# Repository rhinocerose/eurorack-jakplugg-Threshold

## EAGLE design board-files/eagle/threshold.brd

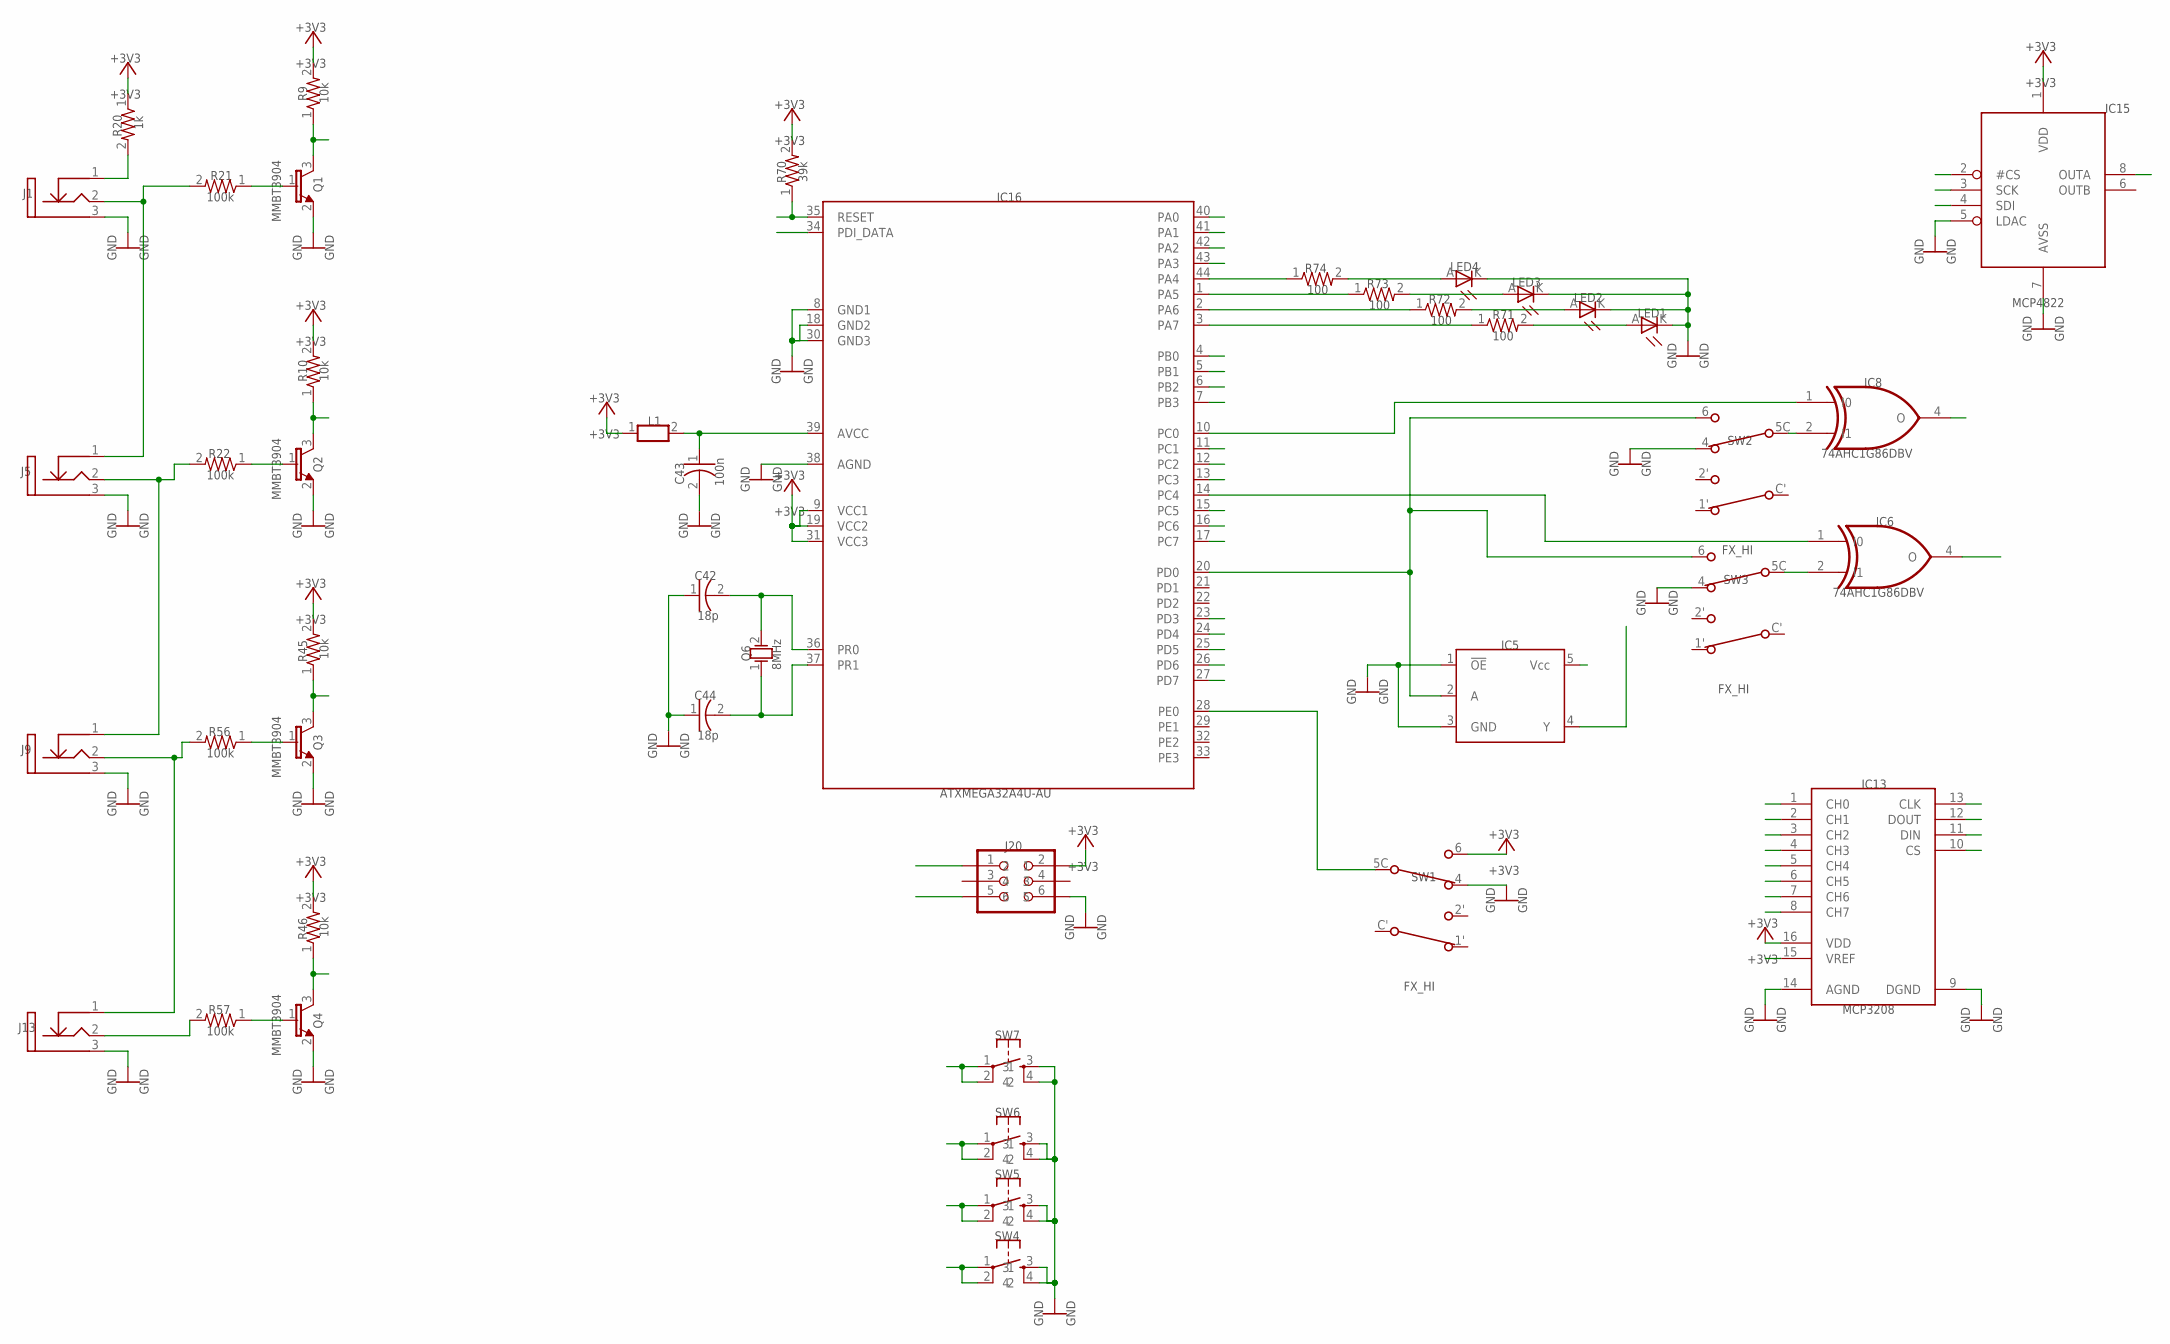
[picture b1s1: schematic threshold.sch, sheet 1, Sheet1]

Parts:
C42, C44: 18p; CAP_0603
C43: 100n; CAP_0603
IC5: 74AHC1G125GV; SOT23-5
IC6, IC8: 74AHC1G86DBV; SOT23-5
IC13: MCP3208; SO16
IC15: MCP4822; SO08
IC16: ATXMEGA32A4U-AU; TQFP44
J1, J5, J9, J13: THONKICONN; THONKICONN_JACK
J20: AVR_SPI_PRG_6PTH; 2X3
L1: WE-CBF_0603; 0603
LED1, LED2, LED3, LED4: LED3MM
Q1, Q2, Q3, Q4: MMBT3904; SOT23
Q6: 8MHz; TSC_7A_CRYSTAL
R9, R10, R45, R46: 10k; RES_0603
R20: 1k; RES_0603
R21, R22, R56, R57: 100k; RES_0603
R70: 39k; RES_0603
R71, R72, R73, R74: 100; RES_0603
SW1, SW2, SW3: FX_HI; PVB6I
SW4, SW5, SW6, SW7: TAC_SWITCHPTH; TACTILE-PTH

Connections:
+3V3: IC5.5 (Vcc), IC13.16 (VDD), IC15.1 (VDD), IC16.9 (VCC1), IC16.19 (VCC2), IC16.31 (VCC3), J20.2, L1.1, R9.2, R10.2, R20.1, R45.2, R46.2, R70.2, SW1.6 (C2); also elsewhere on the board
ADC_MISO: IC13.12 (DOUT), IC16.26 (PD6)
ADC_MOSI: IC13.11 (DIN), IC16.25 (PD5)
ADC_SCK: IC13.13 (CLK), IC16.27 (PD7)
ADC_SS: IC13.10 (CS), IC16.23 (PD3)
AREF: IC13.15 (VREF); also elsewhere on the board
CH1: IC13.1 (CH0); also elsewhere on the board
CH2: IC13.2 (CH1); also elsewhere on the board
CH3: IC13.5 (CH4); also elsewhere on the board
CH4: IC13.6 (CH5); also elsewhere on the board
CH5: IC13.3 (CH2); also elsewhere on the board
CH6: IC13.4 (CH3); also elsewhere on the board
CH7: IC13.7 (CH6); also elsewhere on the board
CH8: IC13.8 (CH7); also elsewhere on the board
CHANNEL1: IC5.4 (Y); also elsewhere on the board
CHANNEL2: IC6.4 (O); also elsewhere on the board
CHANNEL3: IC8.4 (O); also elsewhere on the board
CHANNEL4: IC15.8 (OUTA); also elsewhere on the board
DAC_MOSI: IC15.4 (SDI), IC16.17 (PC7)
DAC_SCK: IC15.3 (SCK), IC16.15 (PC5)
DAC_SS: IC15.2 (#CS), IC16.16 (PC6)
GATE1: IC16.40 (PA0), Q1.3 (C), R9.1
GATE1_IN: J1.2 (Tip), J5.1 (TN), R21.2
GATE1_LED: LED4.A, R74.2
GATE2: IC16.41 (PA1), Q2.3 (C), R10.1
GATE2_IN: J5.2 (Tip), J9.1 (TN), R22.2
GATE2_LED: LED3.A, R73.2
GATE3: IC16.42 (PA2), Q3.3 (C), R45.1
GATE3_IN: J9.2 (Tip), J13.1 (TN), R56.2
GATE3_LED: LED2.A, R72.2
GATE4: IC16.43 (PA3), Q4.3 (C), R46.1
GATE4_IN: J13.2 (Tip), R57.2
GATE4_LED: LED1.A, R71.2
GND: C42.1, C43.2, C44.1, IC5.1 (!OE!), IC5.3 (GND), IC13.9 (DGND), IC13.14 (AGND), IC15.5 (LDAC), IC15.7 (AVSS), IC16.8 (GND1), IC16.18 (GND2), IC16.30 (GND3), IC16.38 (AGND), J1.3 (GND), J5.3 (GND), J9.3 (GND), J13.3 (GND), J20.6, LED1.K (C), LED2.K (C), LED3.K (C), LED4.K (C), Q1.2 (E), Q2.2 (E), Q3.2 (E), Q4.2 (E), SW1.3, SW1.4 (C3), SW2.3, SW2.4 (C3), SW3.3, SW3.4 (C3), SW4.3, SW4.4, SW5.3, SW5.4, SW6.3, SW6.4, SW7.3, SW7.4; also elsewhere on the board
MIDI_IN: IC16.12 (PC2); also elsewhere on the board
unnamed: Q1.1 (B), R21.1
unnamed: Q2.1 (B), R22.1
unnamed: Q3.1 (B), R56.1
unnamed: IC16.44 (PA4), R74.1
unnamed: IC16.1 (PA5), R73.1
unnamed: IC16.2 (PA6), R72.1
unnamed: IC16.3 (PA7), R71.1
unnamed: J1.1 (TN), R20.2
unnamed: IC6.1 (I0), IC16.14 (PC4)
unnamed: IC8.2 (I1), SW2.5C (C1)
unnamed: IC6.2 (I1), SW3.5C (C1)
unnamed: C43.1, IC16.39 (AVCC), L1.2
unnamed: IC8.1 (I0), IC16.10 (PC0)
unnamed: IC5.2 (A), IC16.20 (PD0), SW2.6 (C2), SW3.6 (C2)
unnamed: C44.2, IC16.37 (PR1), Q6.1 (OSC1)
unnamed: C42.2, IC16.36 (PR0), Q6.2 (OSC2)
unnamed: Q4.1 (B), R57.1
NES_TRIANGLE_CLK: IC16.24 (PD4); also elsewhere on the board
PDICLK: IC16.35 (RESET), J20.5, R70.1
PDIDATA: IC16.34 (PDI_DATA), J20.1
SW1: IC16.4 (PB0), SW7.1, SW7.2
SW2: IC16.5 (PB1), SW6.1, SW6.2
SW3: IC16.6 (PB2), SW5.1, SW5.2
SW4: IC16.7 (PB3), SW4.1, SW4.2
SW_MIDI_LEARN: IC16.11 (PC1); also elsewhere on the board
SW_MIDI_MODE: IC16.13 (PC3); also elsewhere on the board
SYNC_SWITCH: IC16.28 (PE0), SW1.5C (C1)

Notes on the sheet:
+3V3
C42
18p
C43
100n
C44
GND
IC5
IC6
74AHC1G86DBV
IC8
IC13
MCP3208
IC15
MCP4822
IC16
ATXMEGA32A4U-AU
J13
J20
LED1
LED2
LED3
LED4
MMBT3904
8MHz
10k
R10
R20
R21
100k
R22
R45
R46
R56
R57
R70
39k
R71
100
R72

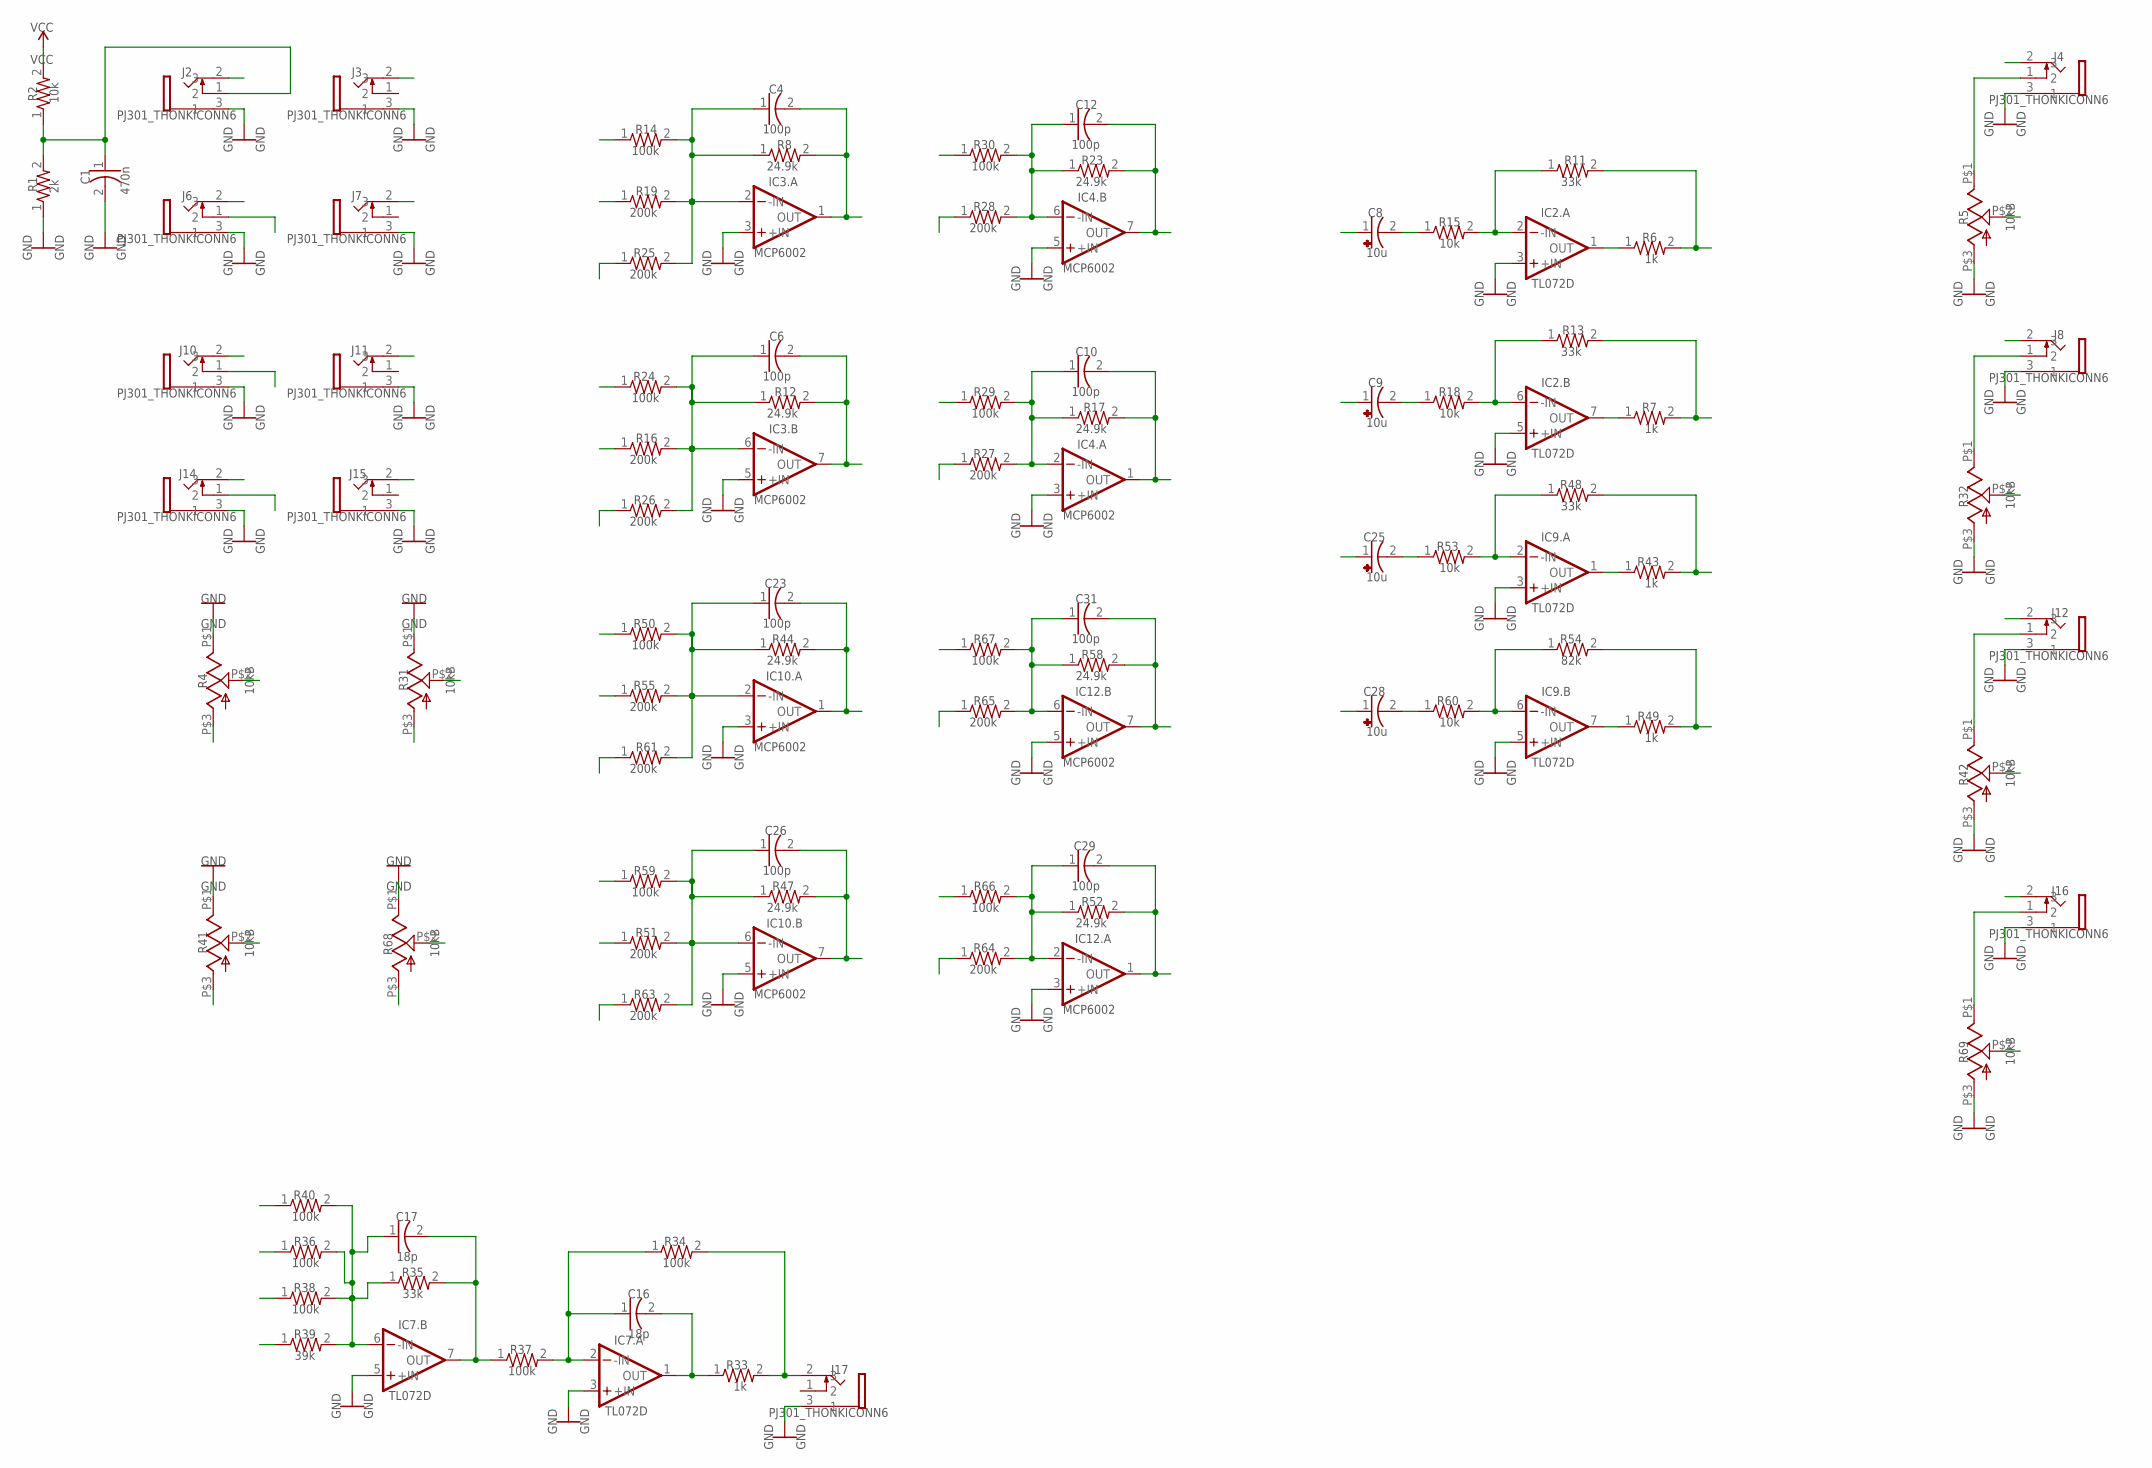
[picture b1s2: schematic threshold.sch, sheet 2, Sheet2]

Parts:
C1: 470n; CAP_0603
C4, C6, C10, C12, C23, C26, C29, C31: 100p; CAP_0603
C8, C9, C25, C28: 10u; CAP_1206
C16, C17: 18p; CAP_0603
IC2, IC7, IC9: TL072D; SO08_23
IC3, IC4, IC10, IC12: MCP6002; SO08_23
J2, J3, J4, J6, J7, J8, J10, J11, J12, J14, J15, J16, J17: PJ301_THONKICONN6; THONKICONN
R1: 2k; RES_0603
R2, R15, R18, R53, R60: 10k; RES_0603
R4, R5, R31, R32, R41, R42, R68, R69: 10kB; ALPS_POT_VERTICAL_PS
R6, R7, R33, R43, R49: 1k; RES_0603
R8, R12, R17, R23, R44, R47, R52, R58: 24.9k; RES_0603
R11, R13, R35, R48: 33k; RES_0603
R14, R24, R29, R30, R34, R36, R37, R38, R40, R50, R59, R66, R67: 100k; RES_0603
R16, R19, R25, R26, R27, R28, R51, R55, R61, R63, R64, R65: 200k; RES_0603
R39: 39k; RES_0603
R54: 82k; RES_0603

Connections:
AREF_-10: R4.P$3 (A), R25.1, R26.1, R27.1, R28.1, R31.P$3 (A), R41.P$3 (A), R61.1, R63.1, R64.1, R65.1, R68.P$3 (A); also elsewhere on the board
CH1: C4.2, IC3.1 (OUT), R8.2; also elsewhere on the board
CH2: C6.2, IC3.7 (OUT), R12.2; also elsewhere on the board
CH3: C23.2, IC10.1 (OUT), R44.2; also elsewhere on the board
CH4: C26.2, IC10.7 (OUT), R47.2; also elsewhere on the board
CH5: C12.2, IC4.7 (OUT), R23.2; also elsewhere on the board
CH6: C10.2, IC4.1 (OUT), R17.2; also elsewhere on the board
CH7: C31.2, IC12.7 (OUT), R58.2; also elsewhere on the board
CH8: C29.2, IC12.1 (OUT), R52.2; also elsewhere on the board
CHANNEL1: C8.1 (+); also elsewhere on the board
CHANNEL1_BUFFERED: J4.2 (3), R6.2, R11.2
CHANNEL1_RETURN: R5.P$2 (S), R40.1
CHANNEL2: C9.1 (+); also elsewhere on the board
CHANNEL2_BUFFERED: J8.2 (3), R7.2, R13.2
CHANNEL2_RETURN: R32.P$2 (S), R36.1
CHANNEL3: C25.1 (+); also elsewhere on the board
CHANNEL3_BUFFERED: J12.2 (3), R43.2, R48.2
CHANNEL3_RETURN: R38.1, R42.P$2 (S)
CHANNEL4: C28.1 (+); also elsewhere on the board
CHANNEL4_BUFFERED: J16.2 (3), R49.2, R54.2
CHANNEL4_RETURN: R39.1, R69.P$2 (S)
COARSE1: R4.P$2 (S), R19.1
COARSE2: R16.1, R31.P$2 (S)
COARSE3: R41.P$2 (S), R55.1
COARSE4: R51.1, R68.P$2 (S)
CV1: J2.2 (3), J6.1 (2), R14.1
CV2: J6.2 (3), J10.1 (2), R24.1
CV3: J10.2 (3), J14.1 (2), R50.1
CV4: J14.2 (3), R59.1
FM1: J3.2 (3), R30.1
FM2: J7.2 (3), R29.1
FM3: J11.2 (3), R67.1
FM4: J15.2 (3), R66.1
GND: C1.2, IC2.3 (+IN), IC2.5 (+IN), IC3.3 (+IN), IC3.5 (+IN), IC4.3 (+IN), IC4.5 (+IN), IC7.3 (+IN), IC7.5 (+IN), IC9.3 (+IN), IC9.5 (+IN), IC10.3 (+IN), IC10.5 (+IN), IC12.3 (+IN), IC12.5 (+IN), J2.3 (1), J3.3 (1), J4.3 (1), J6.3 (1), J7.3 (1), J8.3 (1), J10.3 (1), J11.3 (1), J12.3 (1), J14.3 (1), J15.3 (1), J16.3 (1), J17.3 (1), R1.1, R4.P$1 (E), R4.P$4, R4.P$5, R5.P$3 (A), R5.P$4, R5.P$5, R31.P$1 (E), R31.P$4, R31.P$5, R32.P$3 (A), R32.P$4, R32.P$5, R41.P$1 (E), R41.P$4, R41.P$5, R42.P$3 (A), R42.P$4, R42.P$5, R68.P$1 (E), R68.P$4, R68.P$5, R69.P$3 (A), R69.P$4, R69.P$5; also elsewhere on the board
MIX: J17.2 (3), R33.2, R34.2
unnamed: J8.1 (2), R32.P$1 (E)
unnamed: C23.1, IC10.2 (-IN), R44.1, R50.2, R55.2, R61.2
unnamed: C10.1, IC4.2 (-IN), R17.1, R27.2, R29.2
unnamed: C26.1, IC10.6 (-IN), R47.1, R51.2, R59.2, R63.2
unnamed: C31.1, IC12.6 (-IN), R58.1, R65.2, R67.2
unnamed: C29.1, IC12.2 (-IN), R52.1, R64.2, R66.2
unnamed: C8.2 (-), R15.1
unnamed: IC2.2 (-IN), R11.1, R15.2
unnamed: IC2.1 (OUT), R6.1
unnamed: C9.2 (-), R18.1
unnamed: IC2.6 (-IN), R13.1, R18.2
unnamed: IC2.7 (OUT), R7.1
unnamed: C25.2 (-), R53.1
unnamed: C12.1, IC4.6 (-IN), R23.1, R28.2, R30.2
unnamed: IC9.2 (-IN), R48.1, R53.2
unnamed: IC9.1 (OUT), R43.1
unnamed: C28.2 (-), R60.1
unnamed: IC9.6 (-IN), R54.1, R60.2
unnamed: IC9.7 (OUT), R49.1
unnamed: C17.1, IC7.6 (-IN), R35.1, R36.2, R38.2, R39.2, R40.2
unnamed: C16.1, IC7.2 (-IN), R34.1, R37.2
unnamed: C16.2, IC7.1 (OUT), R33.1
unnamed: J4.1 (2), R5.P$1 (E)
unnamed: C17.2, IC7.7 (OUT), R35.2, R37.1
unnamed: J12.1 (2), R42.P$1 (E)
unnamed: J16.1 (2), R69.P$1 (E)
unnamed: C6.1, IC3.6 (-IN), R12.1, R16.2, R24.2, R26.2
unnamed: C1.1, J2.1 (2), R1.2, R2.1
unnamed: C4.1, IC3.2 (-IN), R8.1, R14.2, R19.2, R25.2
VCC: R2.2; also elsewhere on the board

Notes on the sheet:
470n
100p
10u
C10
C12
C16
18p
C17
C23
C25
C26
C28
C29
C31
GND
IC2.A
TL072D
IC2.B
IC3.A
MCP6002
IC3.B
IC4.A
IC4.B
IC7.A
IC7.B
IC9.A
IC9.B
IC10.A
IC10.B
IC12.A
IC12.B
PJ301_THONKICONN6
J10
J11
J12
J14
J15
J16
J17
VCC

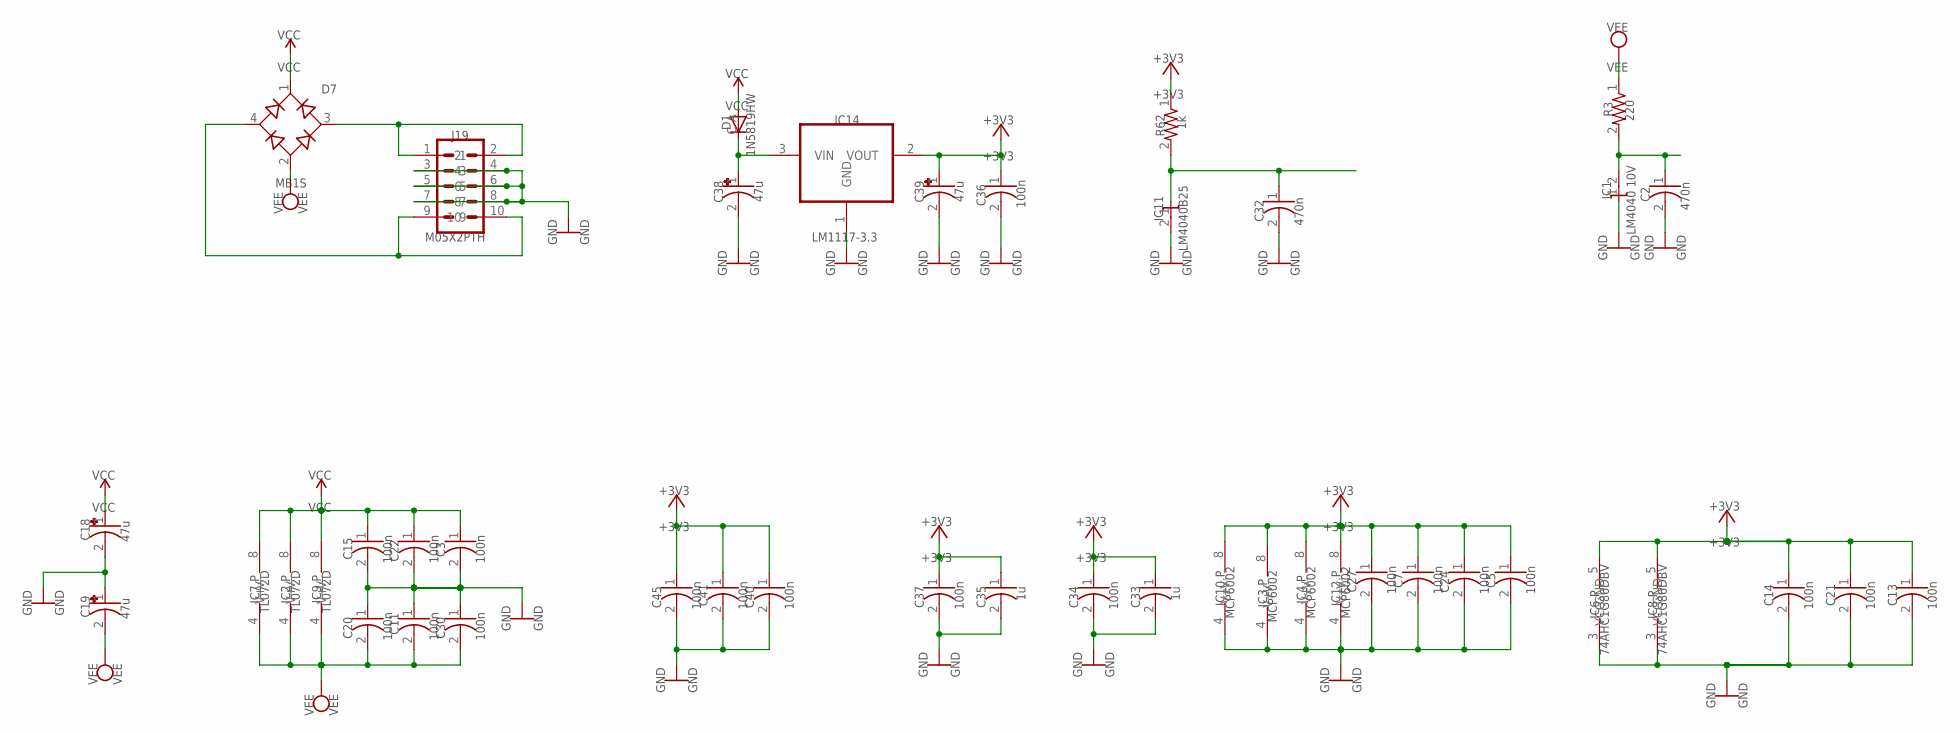
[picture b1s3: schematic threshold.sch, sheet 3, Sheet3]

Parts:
C2, C32: 470n; CAP_0603
C3, C5, C7, C11, C13, C14, C15, C20, C21, C22, C24, C27, C30, C34, C36, C37, C40, C41, C45: 100n; CAP_0603
C18, C19, C38, C39: 47u; CAPAE-5.3X5.3H7
C33, C35: 1u; CAP_0603
D1: 1N5819HW; SOD123
D7: MB1S; SOP-4/6.5X2.54
IC1: LM4040 10V; SOT23
IC2, IC7, IC9: TL072D; SO08_23
IC3, IC4, IC10, IC12: MCP6002; SO08_23
IC6, IC8: 74AHC1G86DBV; SOT23-5
IC11: LM4040B25; SOT23
IC14: LM1117-3.3; SOT223
J19: M05X2PTH; AVR_ICSP
R3: 220; RES_0603
R62: 1k; RES_0603

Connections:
+3V3: C5.1, C7.1, C13.1, C14.1, C21.1, C24.1, C27.1, C33.1, C34.1, C35.1, C36.1, C37.1, C39.1 (+), C40.1, C41.1, C45.1, IC3.8 (V+), IC4.8 (V+), IC6.5 (VCC), IC8.5 (VCC), IC10.8 (V+), IC12.8 (V+), IC14.2 (VOUT), R62.1; also elsewhere on the board
AREF: C32.1, IC11.1 (C), R62.2; also elsewhere on the board
AREF_-10: C2.1, IC1.2 (A), R3.2; also elsewhere on the board
GND: C2.2, C3.2, C5.2, C7.2, C11.1, C13.2, C14.2, C15.2, C18.2 (-), C19.1 (+), C20.1, C21.2, C22.2, C24.2, C27.2, C30.1, C32.2, C33.2, C34.2, C35.2, C36.2, C37.2, C38.2 (-), C39.2 (-), C40.2, C41.2, C45.2, IC1.1 (C), IC3.4 (V-), IC4.4 (V-), IC6.3 (GND), IC8.3 (GND), IC10.4 (V-), IC11.2 (A), IC12.4 (V-), IC14.1 (GND), J19.3, J19.4, J19.5, J19.6, J19.7, J19.8; also elsewhere on the board
unnamed: C38.1 (+), D1.C, IC14.3 (VIN)
Net_101: D7.3 (AC2), J19.1, J19.2
Net_139: D7.4 (AC1), J19.9, J19.10
VCC: C3.1, C15.1, C18.1 (+), C22.1, D1.A, D7.1 (+), IC2.8 (V+), IC7.8 (V+), IC9.8 (V+); also elsewhere on the board
VEE: C11.2, C19.2 (-), C20.2, C30.2, D7.2 (-), IC2.4 (V-), IC7.4 (V-), IC9.4 (V-), R3.1; also elsewhere on the board

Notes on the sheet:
+3V3
470n
100n
C11
C13
C14
C15
C18
47u
C19
C20
C21
C22
C24
C27
C30
C32
C33
C34
C35
C36
C37
C38
C39
C40
C41
C45
1N5819HW
MB1S
GND
IC1
LM4040 10V
IC2.P
TL072D
IC3.P
MCP6002
IC4.P
IC6.P
74AHC1G86DBV
IC7.P

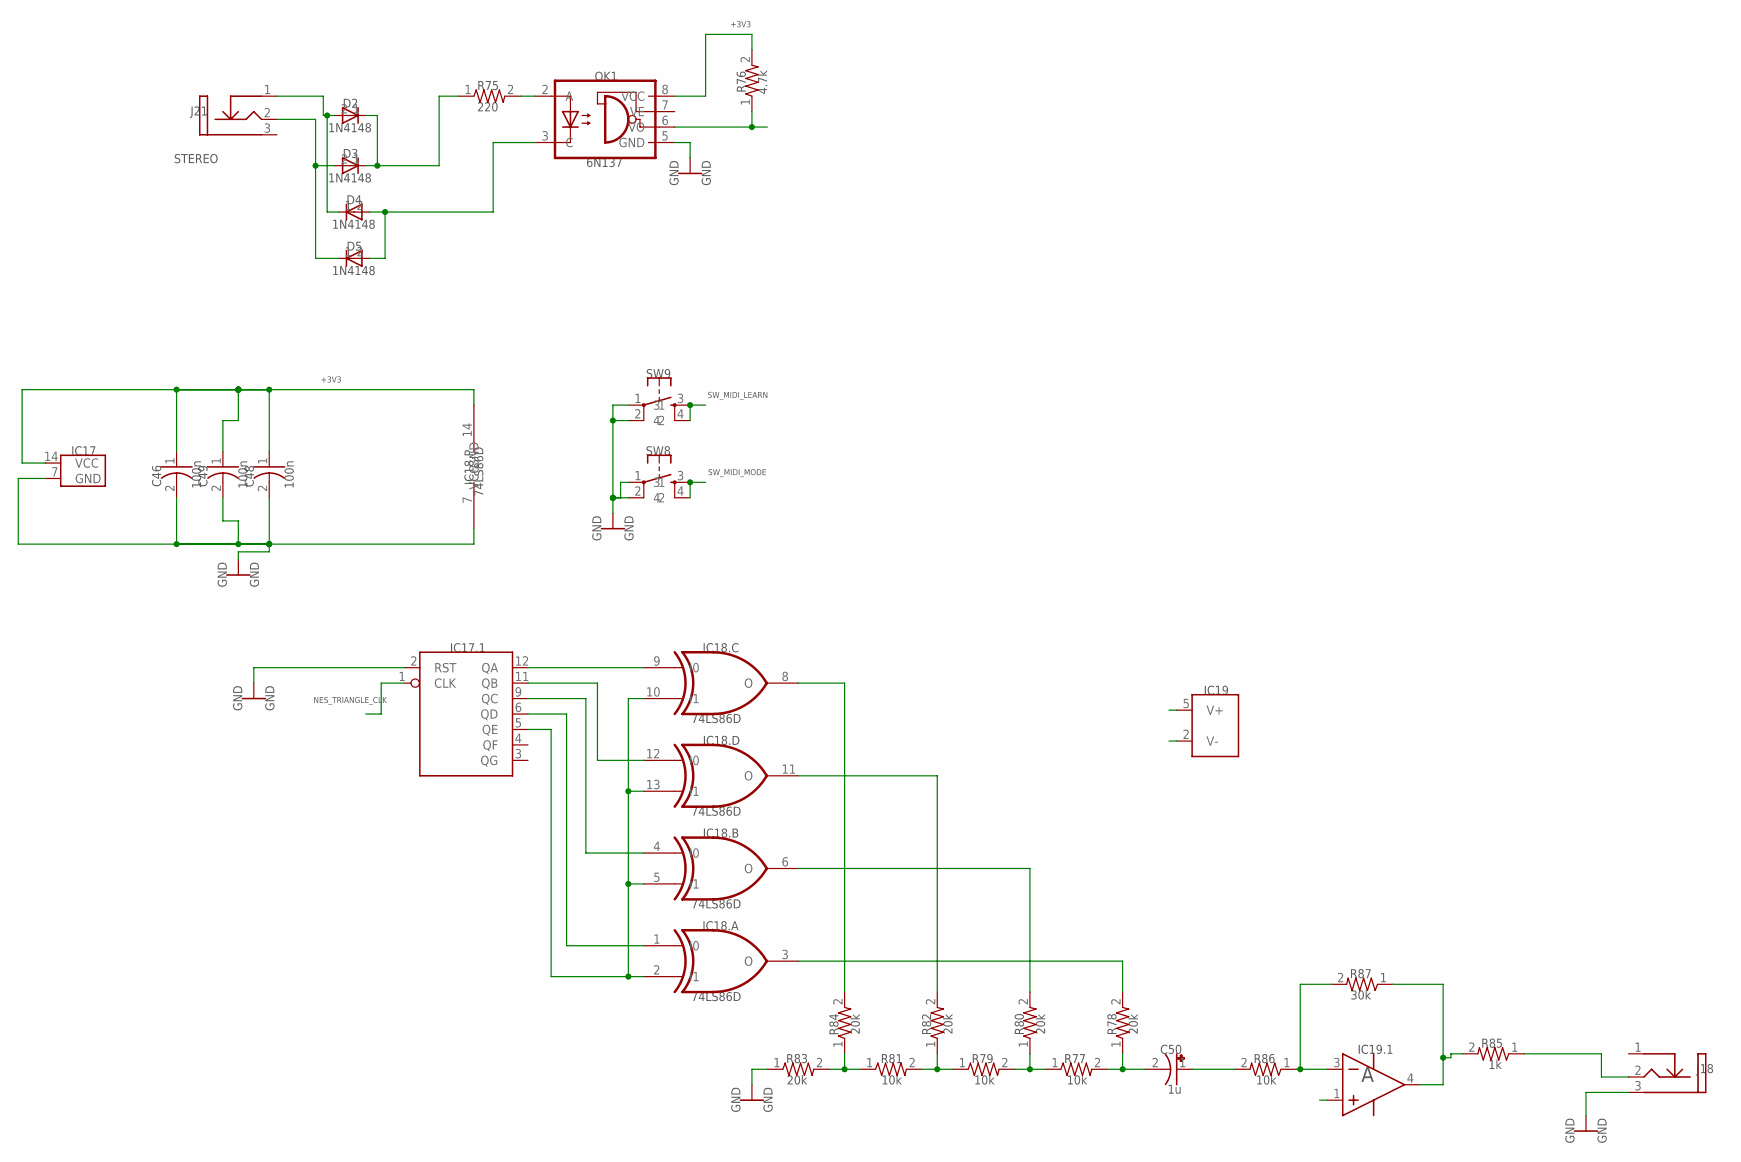
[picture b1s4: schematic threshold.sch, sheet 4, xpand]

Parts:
C46, C48, C49: 100n; CAP_0603
C50: 1u; CAP_0805
D2, D3, D4, D5: 1N4148; SOD-123F
IC17: M74HC4024M1R; SOIC-14/150MIL
IC18: 74LS86D; SOIC-14/150MIL
IC19: LM321MF; SOT23-5
J18: THONKICONN_35; THONKICONN_JACK
J21: STEREO; THONKICONN_JACK
OK1: 6N137; SOIC-8/150MIL
R75: 220; RES_0603
R76: 4.7k; RES_0603
R77, R79, R81, R86: 10k; RES_0603
R78, R80, R82, R83, R84: 20k; RES_0603
R85: 1k; RES_0603
R87: 30k; RES_0603
SW8, SW9: TAC_SWITCHPTH; TACTILE-PTH

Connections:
+3V3: C46.1, C48.1, C49.1, IC17.14 (VCC), IC18.14 (VCC), OK1.8 (VCC), R76.2; also elsewhere on the board
GND: C46.2, C48.2, C49.2, IC17.2 (RST), IC17.7 (GND), IC18.7 (GND), IC19.1 (IN+), J18.3 (GND), OK1.5 (GND), R83.1, SW8.1, SW8.2, SW9.1, SW9.2; also elsewhere on the board
MIDI_IN: OK1.6 (VO), R76.1; also elsewhere on the board
unnamed: IC17.5 (QE), IC18.2 (I1), IC18.5 (I1), IC18.10 (I1), IC18.13 (I1)
unnamed: IC17.11 (QB), IC18.12 (I0)
unnamed: IC17.12 (QA), IC18.9 (I0)
unnamed: IC17.6 (QD), IC18.1 (I0)
unnamed: R81.1, R83.2, R84.1
unnamed: R79.1, R81.2, R82.1
unnamed: R77.1, R79.2, R80.1
unnamed: C50.2 (-), R77.2, R78.1
unnamed: J18.2 (Tip), R85.1
NES_TRIANGLE_CLK: IC17.1 (CLK); also elsewhere on the board
Net_0: IC19.3 (IN-), R86.1, R87.2
Net_1: C50.1 (+), R86.2
Net_56: D4.2 (A), D5.2 (A), OK1.3 (C)
Net_57: D2.1 (C), D3.1 (C), R75.1
Net_113: D2.2 (A), D4.1 (C), J21.1 (TN)
Net_131: IC18.6 (O), R80.2
Net_132: IC18.3 (O), R78.2
Net_133: IC18.11 (O), R82.2
Net_134: IC18.8 (O), R84.2
Net_135: IC19.4 (OUT), R85.2, R87.1
Net_136: D3.2 (A), D5.1 (C), J21.2 (Tip)
Net_137: OK1.2 (A), R75.2
Net_138: IC17.9 (QC), IC18.4 (I0)
SW_MIDI_LEARN: SW9.3, SW9.4; also elsewhere on the board
SW_MIDI_MODE: SW8.3, SW8.4; also elsewhere on the board
VCC: IC19.5 (V+); also elsewhere on the board
VEE: IC19.2 (V-); also elsewhere on the board

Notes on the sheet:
NES_TRIANGLE_CLK
SW_MIDI_MODE
SW_MIDI_LEARN
+3V3
C46
100n
C48
C49
C50
1N4148
GND
IC17.1
IC17
IC18.A
74LS86D
IC18.B
IC18.C
IC18.D
IC18.P
IC19.1
IC19
J18
J21
STEREO
OK1
6N137
R75
220
R76
4.7k
R77
10k
R78
20k
R79
R80
R81
R82
R83
R84

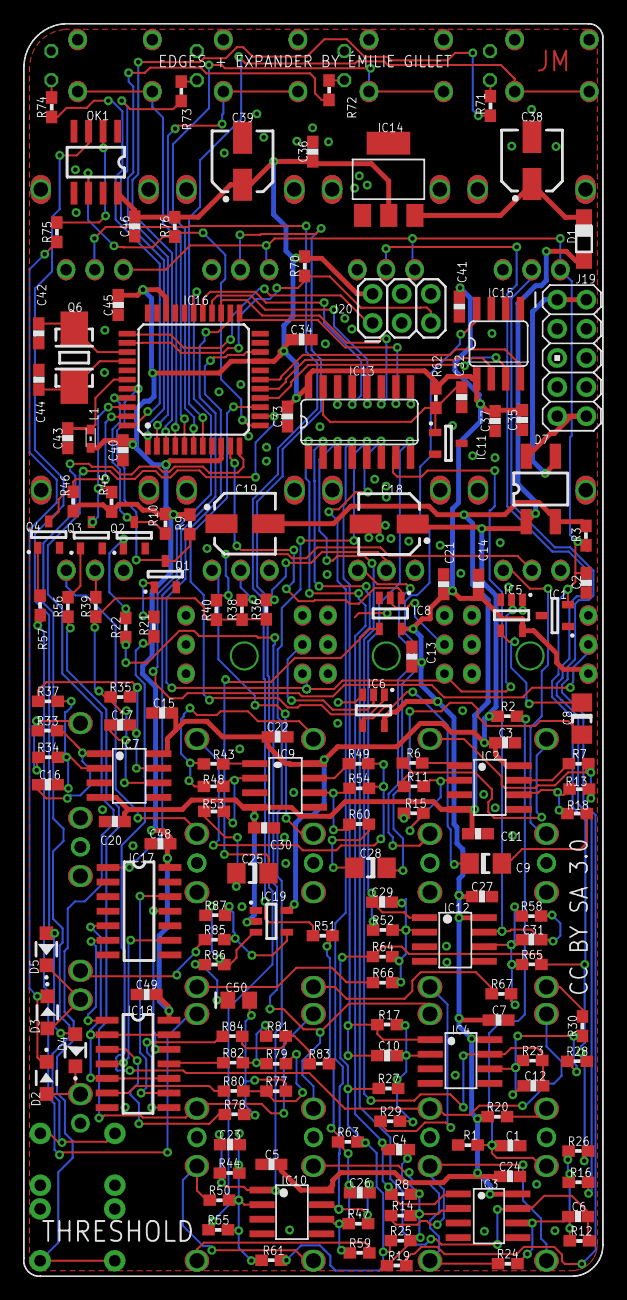
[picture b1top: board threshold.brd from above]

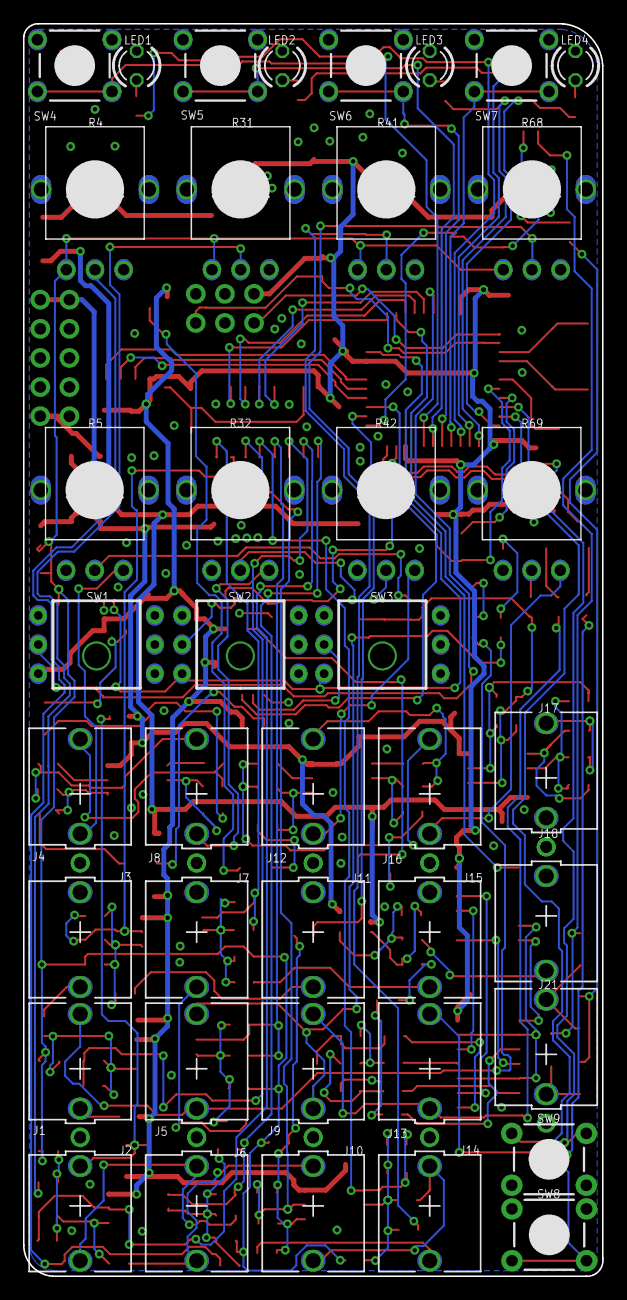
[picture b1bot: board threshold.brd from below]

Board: 2 copper layers, 50.5 x 109.2 mm, 202 parts (40 on the bottom side), 140 nets.

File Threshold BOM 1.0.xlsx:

Quantity | RefDes | Value | Name | Mouser | Digikey | Notes
4.0 | C16, C17, C42, C44 | 18p | C-USC0603 | 81-GRM185C1H180JA01J
8.0 | C4, C6, C10, C12, C23, C26, C29, C31 | 100p | C-USC0603 | 80-C0603C101J4G
23.0 | C3, C5, C7, C11, C13, C14, C15, C20, C21, C22, C24, C27, C30, C34, C36, C37, C4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 | 100n | C-USC0603 | 80-C0603C104M4R
3.0 | C1, C2, C32 | 470n | C-USC0603 | 80-C0603C474M4P
2.0 | C33, C35 | 1u | C-USC0603 | 80-C0603C105Z9V
4.0 | C8, C9, C25, C28 | 10u | C-USC1206 | TMK316ABJ106MD-T
1.0 | C50 | 1u | C-USC0805
4.0 | C18, C19, C38, C39 | 47u | EEE-FT1V470AR | 667-EEE-FT1V470AR
4.0 | R71, R72, R73, R74 | 100.0 | R-US_R0603 | RC0603FR-07100RL
2.0 | R3, R75 | 220.0 | R-US_R0603 | RC0603FR-07220RL
8.0 | R6, R7, R20, R33, R43, R49, R62, R85 | 1k | R-US_R0603 | 603-RC0603FR-071KL
1.0 | R1 | 2k | R-US_R0603 | 603-RC0603FR-072KL
1.0 | R76 | 4.7k | R-US_R0603 | 603-RC0603FR-074k7L
13.0 | R2, R9, R10, R15, R18, R45, R46, R53, R60, R77, R79, R81, R86 | 10k | R-US_R0603 | 603-RC0603FR-0710KL
5.0 | R78, R80, R82, R83, R84 | 20k | R-US_R0603 | 603-RC0603FR-0720KL
8.0 | R8, R12, R17, R23, R44, R47, R52, R58 | 24.9k | R-US_R0603 | 603-RC0603FR-0724k9L
1.0 | R87 | 30k | R-US_R0603 | 603-RC0603FR-0730kL
4.0 | R11, R13, R35, R48 | 33k | R-US_R0603 | 603-RC0603FR-0733KL
2.0 | R39, R70 | 39k | R-US_R0603 | 603-RC0603FR-0739KL
1.0 | R54 | 82k | R-US_R0603 | 603-RC0603FR-0782KL
17.0 | R14, R21, R22, R24, R29, R30, R34, R36, R37, R38, R40, R50, R56, R57, R59, R66,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 | 100k | R-US_R0603 | 603-RC0603FR-07100KL
12.0 | R16, R19, R25, R26, R27, R28, R51, R55, R61, R63, R64, R65 | 200k | R-US_R0603 | 603-RC0603FR-07200KL
8.0 | R4, R5, R31, R32, R41, R42, R68, R69 | 10kB | POT_USVERTICAL_PS
1.0 | OK1 | 6N137 | 6N137SMT | 512-HCPL0600
1.0 | IC5 |  | 74AHC1G125GV | 595-SN74AHC1G125DBVR
2.0 | IC6, IC8 | 74AHC1G86DBV | 74AHC1G86DBV | 595-SN74AHC1G86DBVR
1.0 | IC18 | 74LS86D | 74LS86D | 595-SN74LS86ADR
1.0 | IC16 | ATXMEGA32A4U-AU | AVR_XMEGA_A4_44A | 556-ATXMEGA32A4U-AU
1.0 | D1 | 1N5819HW | DIODE-SOD123 | 621-1N5819HW-F
4.0 | D2, D3, D4, D5 | 1N4148 | DIODE-SOD123 | 78-1N4148W-HE3-08
4.0 | LED1, LED2, LED3, LED4 |  | LED3MM | 604-WP424GDT
1.0 | IC19 |  | LM321MF | 926-LM321MFX/NOPB
1.0 | IC11 | LM4040B25 | LM4041B12DBZ | 595-LM4040C25IDBZR
1.0 | IC1 | LM4040 10V | LM4041C12DBZ | 595-LM4040C10IDBZR
1.0 | IC17 | 74HC4024 | M74HC4024M1R | 595-CD74HC4024M96
1.0 | D7 | MB1S | MB1S | 512-MB1S
1.0 | IC13 | MCP3208 | MCP3208 | 579-MCP3208T-CI/SL
1.0 | IC15 | MCP4822 | MCP4822SO08 | 579-MCP4822-E/SN
4.0 | Q1, Q2, Q3, Q4 | MMBT3904 | MMBT3904 | 863-MMBT3904LT1G
3.0 | SW1, SW2, SW3 | FX_HI | PVB6 | 667-ESB-33133
3.0 |  |  | Black Switch Cap | 611-PVBK
1.0 | IC14 | LM1117-3.3 | REG1117 | 926-LM1117MPX3.3NOPB
6.0 | SW4, SW5, SW6, SW7, SW8, SW9 |  | TAC_SWITCHPTH | 612-TL1105SP-250
6.0 |  |  | Black Switch Cap | 1RBLK
3.0 | IC2, IC7, IC9 | TL072D | TL072D | 595-TL072CD
4.0 | IC3, IC4, IC10, IC12 | MCP6002 | MCP6002 | 579-MCP6002-I/SN
1.0 | Q6 | 8MHz | TXC 7A crystal | 717-7A-8.000MAAJ-T
1.0 | L1 |  | WE-CBF_0603 | 710-742792642
1.0 |  | M05X2PTH | M05X2PTH
1.0 |  |  | AVR_SPI_PRG_6PTH
18.0 | J1, J5, J9, J13, J18, J2, J3, J4, J6, J7, J8, J10, J11, J12, J14, J15, J16, J17 | PJ301 | PJ301_THONKICONN6
1.0 |  | STEREO | Thonkiconn

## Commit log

2025-08-07 Kicad

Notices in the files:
board-files/eagle/threshold.brd:
CC BY SA 3.0
